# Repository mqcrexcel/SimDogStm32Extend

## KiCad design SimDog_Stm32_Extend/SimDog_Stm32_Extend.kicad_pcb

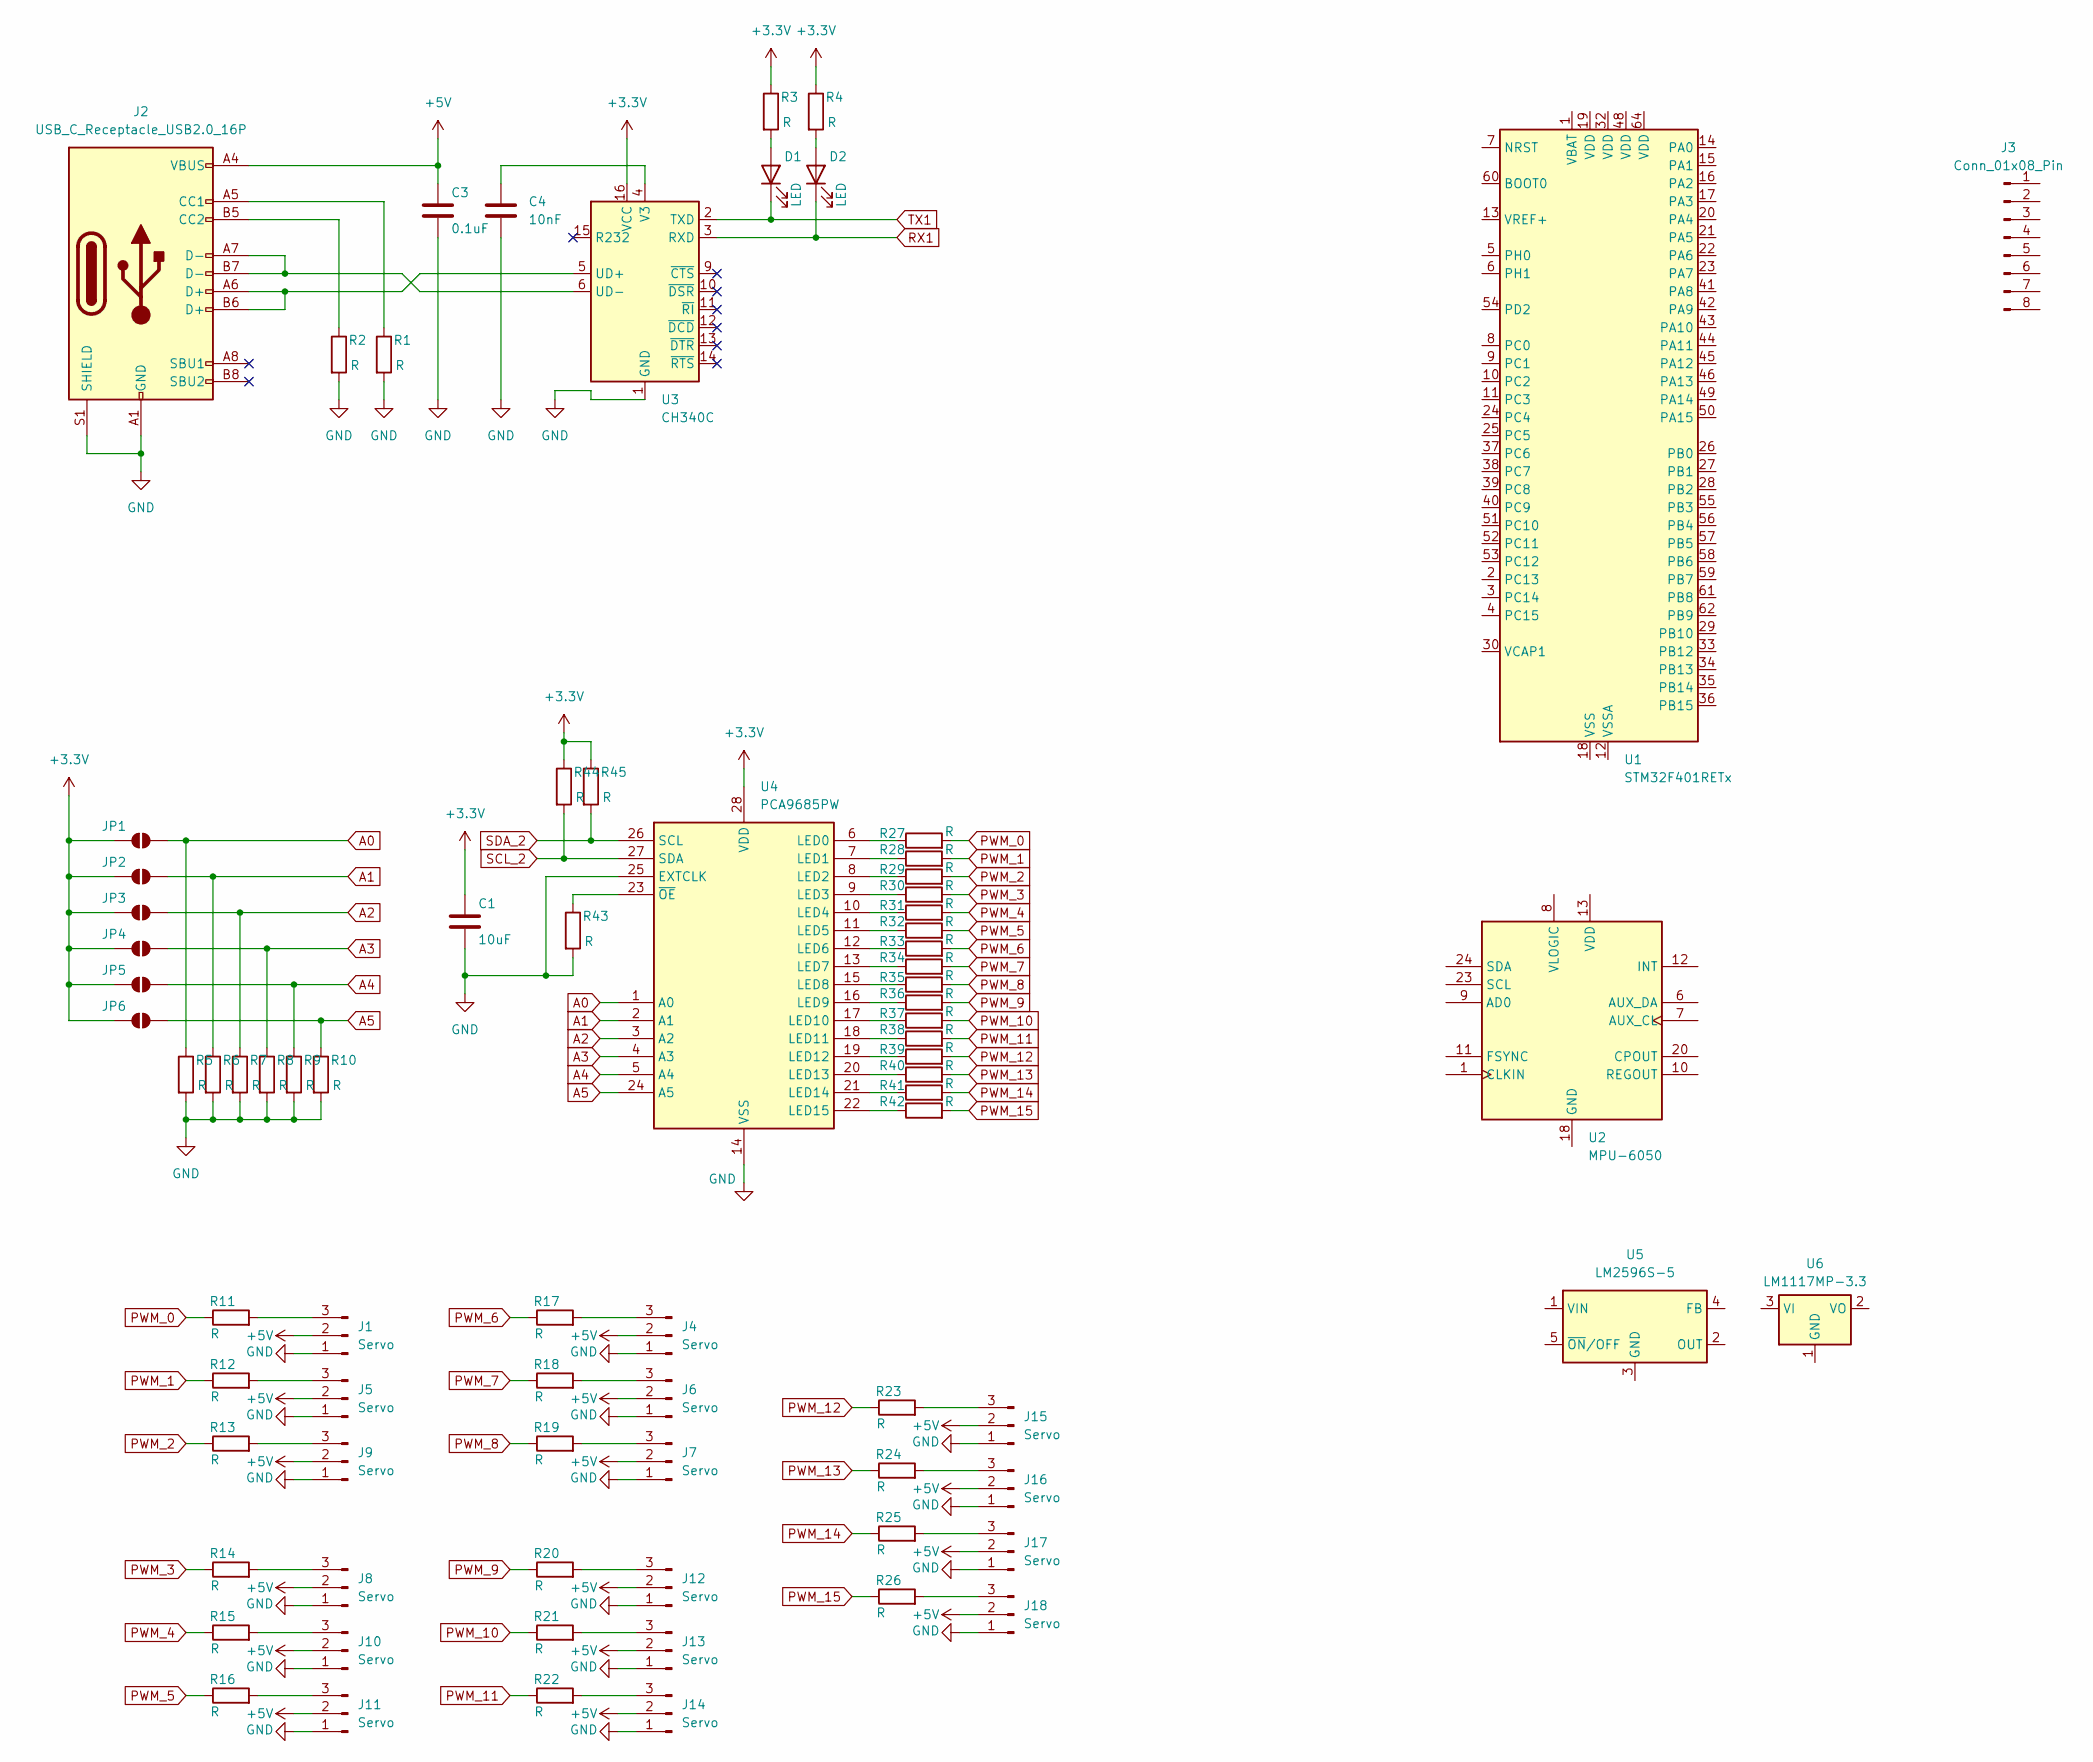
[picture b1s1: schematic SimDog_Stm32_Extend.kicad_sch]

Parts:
C1: 10uF; C_0805_2012Metric_Pad1.18x1.45mm_HandSolder
C3: 0.1uF; C_0603_1608Metric_Pad1.08x0.95mm_HandSolder
C4: 10nF; C_0603_1608Metric_Pad1.08x0.95mm_HandSolder
D1, D2: LED; LED_0603_1608Metric_Pad1.05x0.95mm_HandSolder
J1, J4, J5, J6, J7, J8, J9, J10, J11, J12, J13, J14, J15, J16, J17, J18: Servo; PinHeader_1x03_P2.54mm_Vertical
J2: USB_C_Receptacle_USB2.0_16P; USB_C_Receptacle_GCT_USB4105-xx-A_16P_TopMnt_Horizontal
J3: Conn_01x08_Pin; PinHeader_1x08_P2.54mm_Vertical
JP1, JP2, JP3, JP4, JP5, JP6: SolderJumper_2_Open; SolderJumper-2_P1.3mm_Open_RoundedPad1.0x1.5mm
R1, R2, R3, R4, R5, R6, R7, R8, R9, R10, R11, R12, R13, R14, R15, R16, R17, R18, R19, R20, R21, R22, R23, R24, R25, R26, R27, R28, R29, R30, R31, R32, R33, R34, R35, R36, R37, R38, R39, R40, R41, R42, R43, R44, R45: R; R_0603_1608Metric_Pad0.98x0.95mm_HandSolder
U1: STM32F401RETx; LQFP-64_10x10mm_P0.5mm
U2: MPU-6050; InvenSense_QFN-24_4x4mm_P0.5mm
U3: CH340C; SOIC-16_3.9x9.9mm_P1.27mm
U4: PCA9685PW; TSSOP-28_4.4x9.7mm_P0.65mm
U5: LM2596S-5; TO-263-5_TabPin3
U6: LM1117MP-3.3; SOT-223-3_TabPin2

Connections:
+3.3V: C1.1, JP1.1 (A), JP2.1 (A), JP3.1 (A), JP4.1 (A), JP5.1 (A), JP6.1 (A), R3.1, R4.1, R44.1, R45.1, U3.16 (VCC), U4.28 (VDD)
+5V: C3.1, J1.2, J2.A4 (VBUS), J2.A9 (VBUS), J2.B4 (VBUS), J2.B9 (VBUS), J4.2, J5.2, J6.2, J7.2, J8.2, J9.2, J10.2, J11.2, J12.2, J13.2, J14.2, J15.2, J16.2, J17.2, J18.2
A0: JP1.2 (B), R5.1, U4.1 (A0)
A1: JP2.2 (B), R6.1, U4.2 (A1)
A2: JP3.2 (B), R7.1, U4.3 (A2)
A3: JP4.2 (B), R8.1, U4.4 (A3)
A4: JP5.2 (B), R9.1, U4.5 (A4)
A5: JP6.2 (B), R10.1, U4.24 (A5)
GND: C1.2, C3.2, C4.2, J1.1, J2.A1 (GND), J2.A12 (GND), J2.B1 (GND), J2.B12 (GND), J2.S1 (SHIELD), J4.1, J5.1, J6.1, J7.1, J8.1, J9.1, J10.1, J11.1, J12.1, J13.1, J14.1, J15.1, J16.1, J17.1, J18.1, R1.2, R2.2, R5.2, R6.2, R7.2, R8.2, R9.2, R10.2, R43.2, U3.1 (GND), U4.14 (VSS), U4.25 (EXTCLK)
unnamed: D1.2 (A), R3.2
unnamed: D2.2 (A), R4.2
unnamed: J1.3, R11.2
unnamed: J2.A5 (CC1), R1.1
unnamed: J2.B5 (CC2), R2.1
unnamed: J4.3, R17.2
unnamed: J5.3, R12.2
unnamed: J6.3, R18.2
unnamed: J7.3, R19.2
unnamed: J8.3, R14.2
unnamed: J9.3, R13.2
unnamed: J10.3, R15.2
unnamed: J11.3, R16.2
unnamed: J12.3, R20.2
unnamed: J13.3, R21.2
unnamed: J14.3, R22.2
unnamed: J15.3, R23.2
unnamed: J16.3, R24.2
unnamed: J17.3, R25.2
unnamed: J18.3, R26.2
unnamed: U1.18 (VSS), U1.31 (VSS), U1.47 (VSS), U1.63 (VSS)
unnamed: J2.A6 (D+), J2.B6 (D+), U3.5 (UD+)
unnamed: J2.A7 (D-), J2.B7 (D-), U3.6 (UD-)
unnamed: C4.1, U3.4 (V3)
unnamed: R27.1, U4.6 (LED0)
unnamed: R28.1, U4.7 (LED1)
unnamed: R29.1, U4.8 (LED2)
unnamed: R30.1, U4.9 (LED3)
unnamed: R31.1, U4.10 (LED4)
unnamed: R32.1, U4.11 (LED5)
unnamed: R33.1, U4.12 (LED6)
unnamed: R34.1, U4.13 (LED7)
unnamed: R35.1, U4.15 (LED8)
unnamed: R36.1, U4.16 (LED9)
unnamed: R37.1, U4.17 (LED10)
unnamed: R38.1, U4.18 (LED11)
unnamed: R39.1, U4.19 (LED12)
unnamed: R40.1, U4.20 (LED13)
unnamed: R41.1, U4.21 (LED14)
unnamed: R42.1, U4.22 (LED15)
unnamed: R43.1, U4.23 (~OE)
PWM_0: R11.1, R27.2
PWM_1: R12.1, R28.2
PWM_2: R13.1, R29.2
PWM_3: R14.1, R30.2
PWM_4: R15.1, R31.2
PWM_5: R16.1, R32.2
PWM_6: R17.1, R33.2
PWM_7: R18.1, R34.2
PWM_8: R19.1, R35.2
PWM_9: R20.1, R36.2
PWM_10: R21.1, R37.2
PWM_11: R22.1, R38.2
PWM_12: R23.1, R39.2
PWM_13: R24.1, R40.2
PWM_14: R25.1, R41.2
PWM_15: R26.1, R42.2
RX1: D2.1 (K), U3.3 (RXD)
SCL_2: R44.2, U4.27 (SDA)
SDA_2: R45.2, U4.26 (SCL)
TX1: D1.1 (K), U3.2 (TXD)

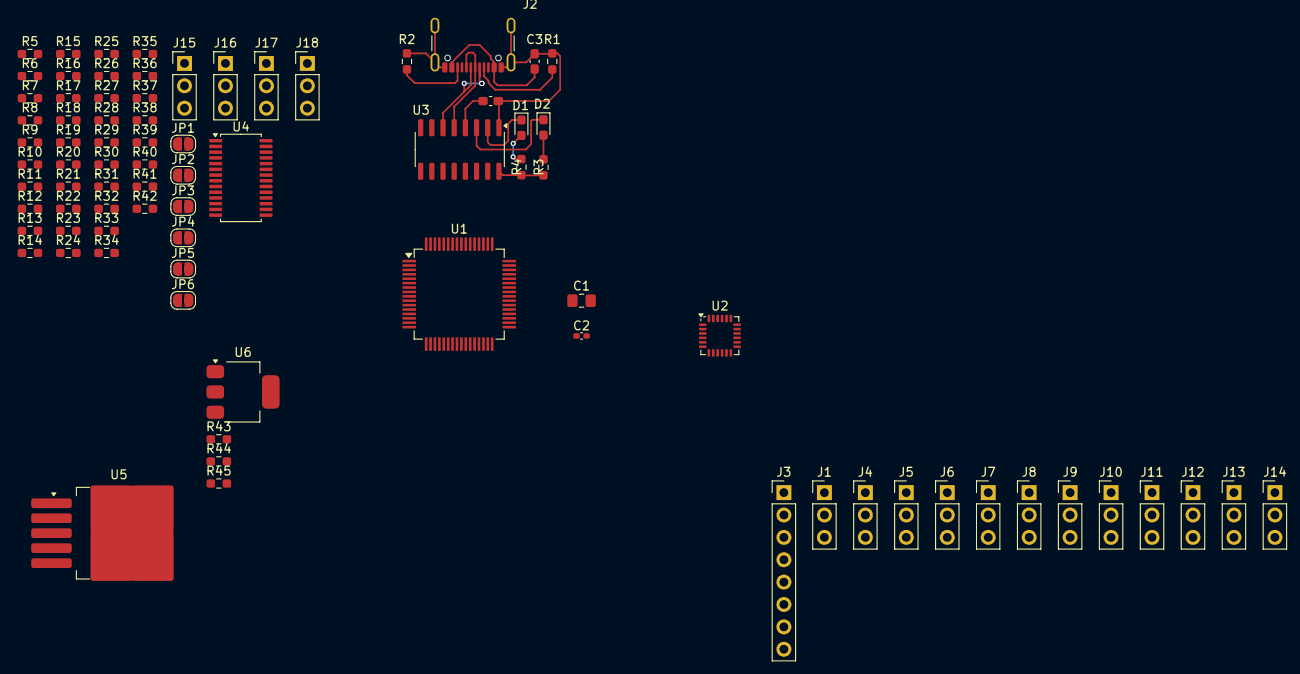
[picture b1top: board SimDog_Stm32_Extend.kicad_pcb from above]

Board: 2 copper layers, 81 parts (0 on the bottom side), 70 nets.

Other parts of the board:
C2: 10nF 0402; C_0402_1005Metric_Pad0.74x0.62mm_HandSolder

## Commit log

2025-04-08 First update
2025-04-08 Add .gitignore
2025-04-08 Remove all backup file
